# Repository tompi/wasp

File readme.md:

The Wasp
--------

It's small, black and yellow and it might sting you.

This is an attempt to make a dirt cheap split keyboard.
There is only one blackpill, keys on the other side are
wired via an RJ45 connector.

Builtin tenting and spikes using 2 pcbs per side, connected
in a 90 degree angle using double row pin header connectors.

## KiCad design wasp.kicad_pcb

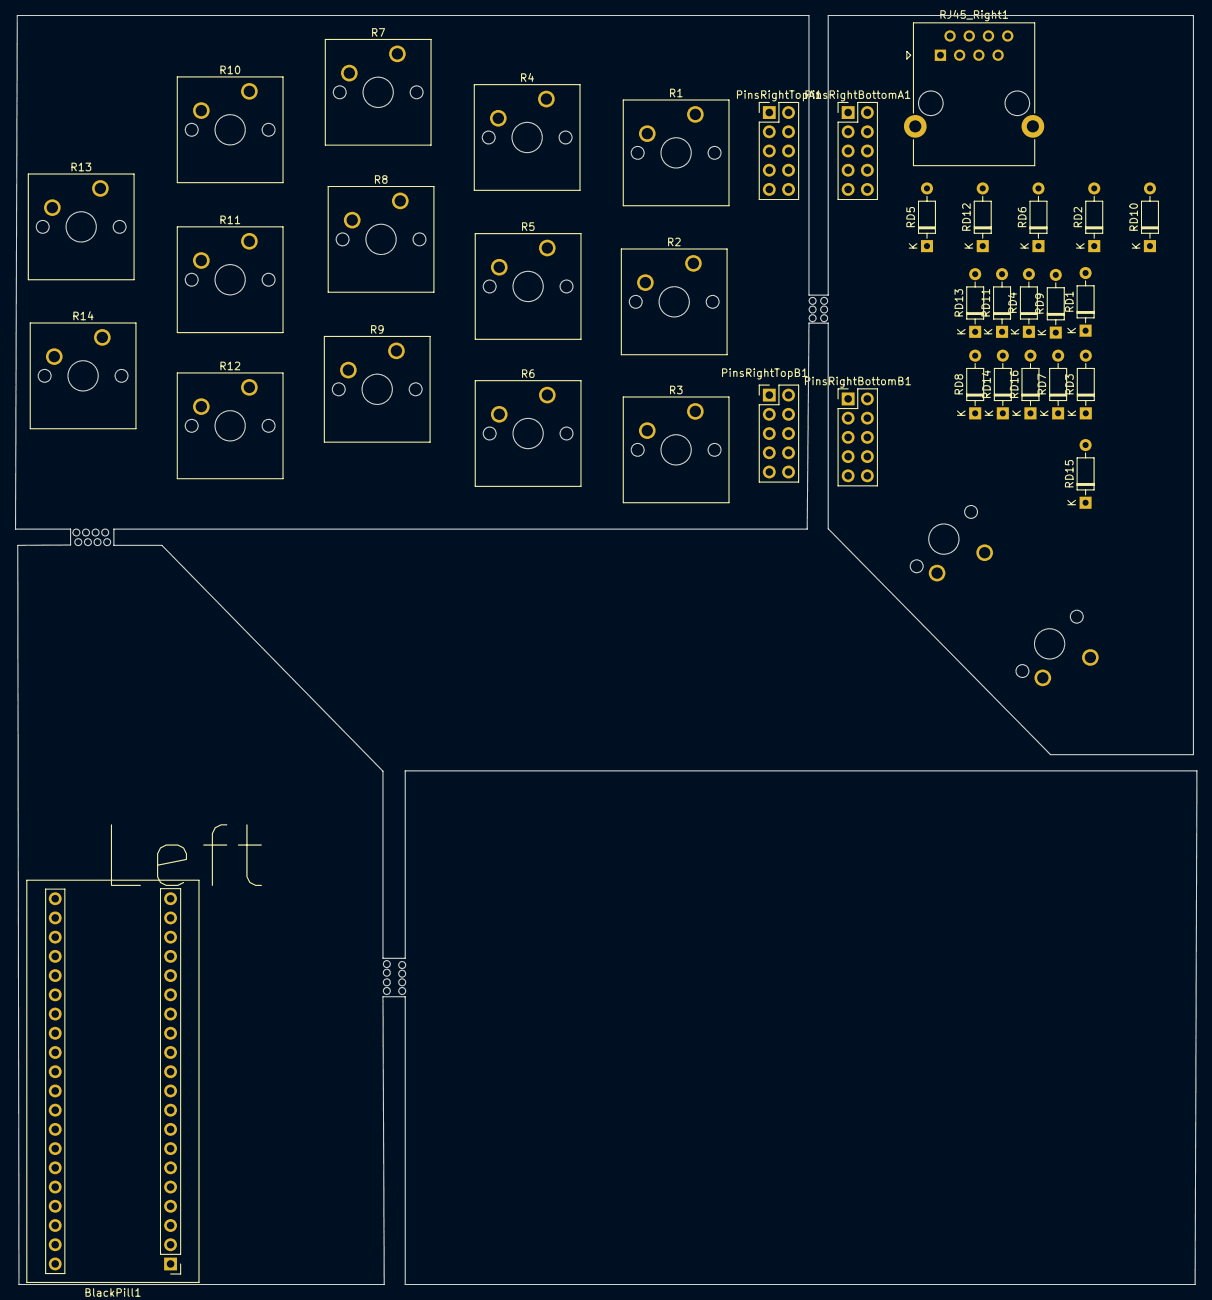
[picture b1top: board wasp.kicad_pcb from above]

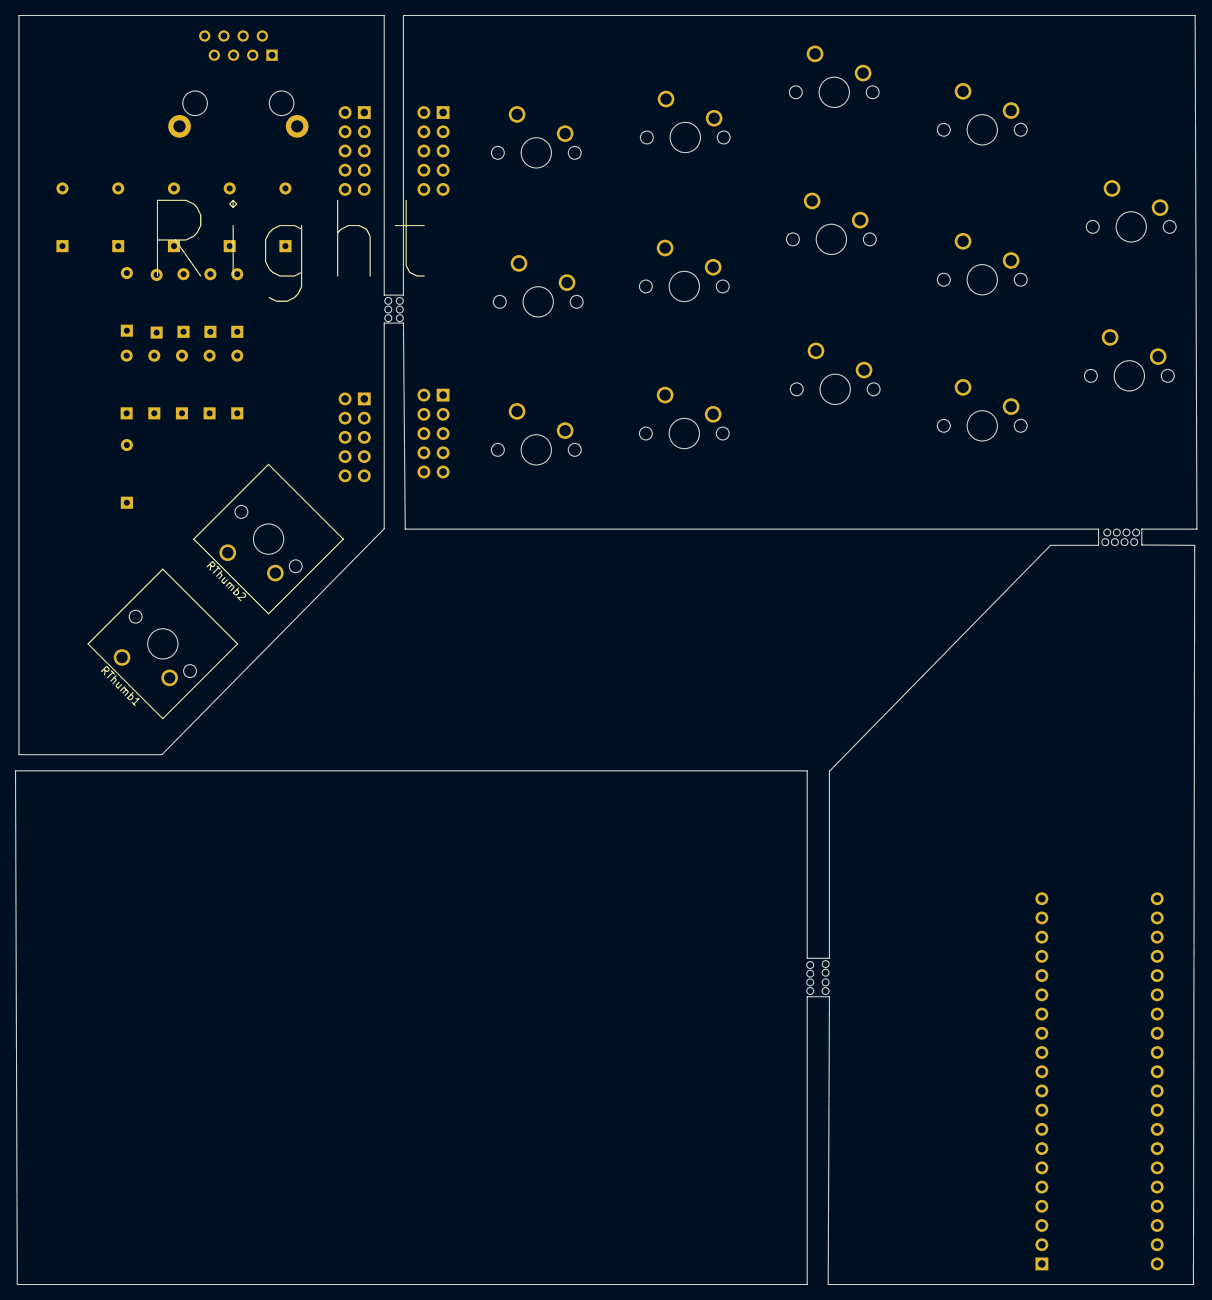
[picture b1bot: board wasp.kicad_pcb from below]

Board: 2 copper layers, 156.1 x 167.7 mm, 38 parts (2 on the bottom side), 42 nets, no tracks yet.

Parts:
BlackPill1: YAAJ_WeAct_BlackPill_Part_Like; YAAJ_WeAct_BlackPill_2
PinsRightBottomA1: Conn_02x05_Odd_Even; PinHeader_2x05_P2.54mm_Vertical
PinsRightBottomB1: Conn_02x05_Odd_Even; PinHeader_2x05_P2.54mm_Vertical
PinsRightTopA1: Conn_02x05_Odd_Even; PinHeader_2x05_P2.54mm_Vertical
PinsRightTopB1: Conn_02x05_Odd_Even; PinHeader_2x05_P2.54mm_Vertical
R1, R2, R3, R4, R5, R6, R7, R8, R9, R10, R11, R12, R13, R14: SW_Push; SW_Cherry_MX_1.00u_PCB
RD1, RD2, RD3, RD4, RD5, RD6, RD7, RD8, RD9, RD10, RD11, RD12, RD13, RD14, RD15, RD16: DIODE; D_DO-35_SOD27_P7.62mm_Horizontal
RJ45_Right1: 8P8C_Shielded; RJ45_Ninigi_GE
RThumb1, RThumb2: SW_Push; SW_Cherry_MX_1.00u_PCB

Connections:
/RB1: PinsRightBottomA1.3, RD1.1 (K)
/RB2: PinsRightBottomA1.5, RD5.1 (K)
/RB3: PinsRightBottomA1.7, RD9.1 (K)
/RB4: PinsRightBottomA1.4, RD2.1 (K)
/RB5: PinsRightBottomA1.6, RD6.1 (K)
/RB6: PinsRightBottomA1.8, RD10.1 (K)
/RB7: PinsRightBottomB1.3, RD3.1 (K)
/RB8: PinsRightBottomB1.5, RD7.1 (K)
/RB9: PinsRightBottomB1.7, RD11.1 (K)
/RB10: PinsRightBottomB1.4, RD4.1 (K)
/RB11: PinsRightBottomB1.6, RD8.1 (K)
/RB12: PinsRightBottomB1.8, RD12.1 (K)
/RB13: PinsRightBottomB1.9, RD13.1 (K)
/RB14: PinsRightBottomB1.10, RD14.1 (K)
/RBC1: PinsRightBottomA1.1, RJ45_Right1.1, RThumb2.1
/RBC2: PinsRightBottomA1.2, RJ45_Right1.2, RThumb1.1
/RBC3: PinsRightBottomB1.1, RJ45_Right1.3
/RBC4: PinsRightBottomB1.2, RJ45_Right1.4
/RBT1: RD15.1 (K), RThumb1.2
/RBT2: RD16.1 (K), RThumb2.2
/RR1: RD1.2 (A), RD2.2 (A), RD3.2 (A), RD4.2 (A), RJ45_Right1.5
/RR2: RD5.2 (A), RD6.2 (A), RD7.2 (A), RD8.2 (A), RJ45_Right1.6
/RR3: RD9.2 (A), RD10.2 (A), RD11.2 (A), RD12.2 (A), RJ45_Right1.7
/RR4: RD13.2 (A), RD14.2 (A), RD15.2 (A), RD16.2 (A), RJ45_Right1.8
/RT1: PinsRightTopA1.3, R1.2
/RT2: PinsRightTopA1.5, R2.2
/RT3: PinsRightTopA1.7, R3.2
/RT4: PinsRightTopA1.4, R4.2
/RT5: PinsRightTopA1.6, R5.2
/RT6: PinsRightTopA1.8, R6.2
/RT7: PinsRightTopB1.3, R7.2
/RT8: PinsRightTopB1.5, R8.2
/RT9: PinsRightTopB1.7, R9.2
/RT10: PinsRightTopB1.4, R10.2
/RT11: PinsRightTopB1.6, R11.2
/RT12: PinsRightTopB1.8, R12.2
/RT13: PinsRightTopB1.9, R13.2
/RT14: PinsRightTopB1.10, R14.2
/RTC1: PinsRightTopA1.1, R1.1, R2.1, R3.1
/RTC2: PinsRightTopA1.2, R4.1, R5.1, R6.1
/RTC3: PinsRightTopB1.1, R7.1, R8.1, R9.1, R13.1
/RTC4: PinsRightTopB1.2, R10.1, R11.1, R12.1, R14.1

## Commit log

2022-02-12 Initial commit: yellow pcbs :)
2022-02-12 Cutouts
2022-02-13 All components
2022-02-13 Named everything and fixed some directions
2022-02-16 Schematics WIP
2022-02-20 Schematics right side
2022-02-24 Finished schematic?
2022-02-24 readme
2022-02-24 Rename file
2022-02-26 Schema finished and ERC passes, removed usage ofunusable pins on blackpill
